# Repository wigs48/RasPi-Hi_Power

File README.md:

# RasPi-Hi_Power
8 channel MOSFET switch hat for RPi

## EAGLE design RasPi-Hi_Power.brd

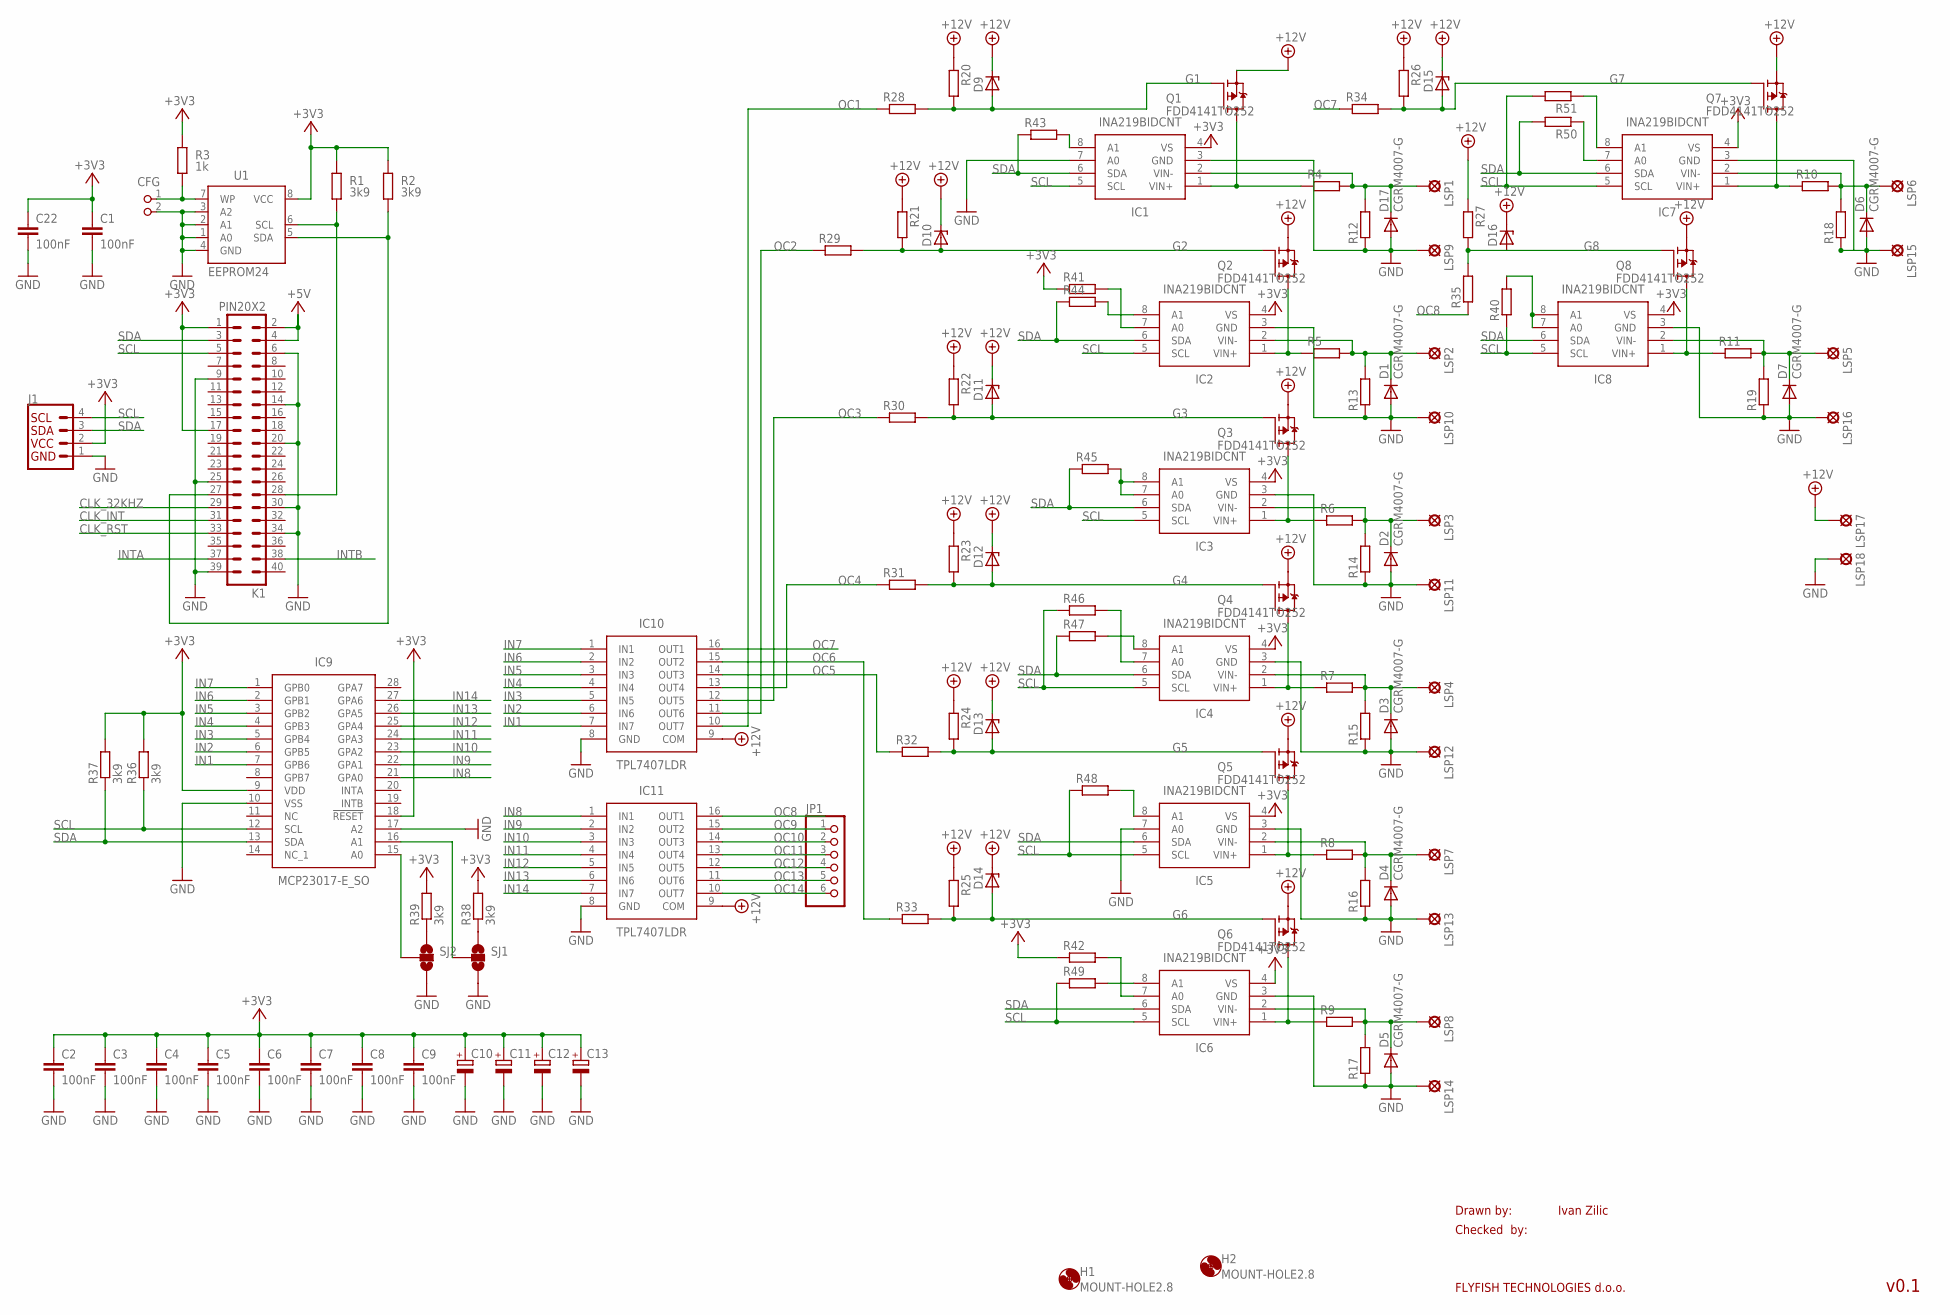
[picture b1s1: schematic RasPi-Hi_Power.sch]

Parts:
C1, C2, C3, C4, C5, C6, C7, C8, C9, C22: 100nF; C0805K
C10, C11, C12, C13: CPOL-EUSMCD; SMC_D
CFG: PIN2_100; PIN_W_2
D1, D2, D3, D4, D5, D6, D7, D17: CGRM4007-G; SOD-123_MINI-SMA
D9, D10, D11, D12, D13, D14, D15, D16: ZENER-DIODESOT23; SOT23
H1, H2: MOUNT-HOLE2.8; 2,8
IC1, IC2, IC3, IC4, IC5, IC6, IC7, IC8: INA219BIDCNT; SOT65P280X145-8N
IC9: MCP23017-E_SO; SOIC127P1030X265-28N
IC10, IC11: TPL7407LDR; SOIC127P600X175-16N
J1: I2C_STANDARD; 1X04
JP1: PINHD-1X6; 1X06
K1: PIN20X2; PIN_20X2
LSP1, LSP2, LSP3, LSP4, LSP5, LSP6, LSP7, LSP8, LSP9, LSP10, LSP11, LSP12, LSP13, LSP14, LSP15, LSP16, LSP17, LSP18: SE13
Q1, Q2, Q3, Q4, Q5, Q6, Q7, Q8: FDD4141TO252; TO252
R1, R2, R36, R37: 3k9; M0805; TOLERANCE 5%
R3: 1k; M0805; TOLERANCE 5%
R4, R5, R6, R7, R8, R9, R10, R11: R-EU_R1210; R1210
R12, R13, R14, R15, R16, R17, R18, R19, R20, R21, R22, R23, R24, R25, R26, R27, R28, R29, R30, R31, R32, R33, R34, R35, R41, R42, R43, R44, R45, R46, R47, R48, R49, R50, R51: R-EU_R0805; R0805
R38, R39: 3k9; R0603; TOLERANCE 5%
R40: R-EU_R0603; R0603
SJ1, SJ2: SOLDERJUMPER_2WAYT; SJ_2
U1: EEPROM24; SOIC8

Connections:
+3V3: C1.1, C2.1, C3.1, C4.1, C5.1, C6.1, C7.1, C8.1, C9.1, C10.+, C11.+, C12.+, C13.+, C22.1, IC1.4 (VS), IC2.4 (VS), IC3.4 (VS), IC4.4 (VS), IC5.4 (VS), IC6.4 (VS), IC7.4 (VS), IC8.4 (VS), IC9.9 (VDD), IC9.18 (!RESET), J1.2, K1.1, K1.17, R1.2, R2.2, R3.2, R36.2, R37.2, R38.2, R39.2, R41.1, R42.1, U1.8 (VCC)
+5V: K1.2, K1.4
+12V: D9.3 (C), D10.3 (C), D11.3 (C), D12.3 (C), D13.3 (C), D14.3 (C), D15.3 (C), D16.3 (C), IC10.9 (COM), IC11.9 (COM), LSP17.MP, Q1.2 (S), Q2.2 (S), Q3.2 (S), Q4.2 (S), Q5.2 (S), Q6.2 (S), Q7.2 (S), Q8.2 (S), R20.1, R21.1, R22.1, R23.1, R24.1, R25.1, R26.1, R27.1
CLK_32KHZ: K1.29
CLK_INT: K1.31
CLK_RST: K1.33
G1: D9.1 (A), Q1.1 (G), R20.2, R28.2
G2: D10.1 (A), Q2.1 (G), R21.2, R29.2
G3: D11.1 (A), Q3.1 (G), R22.2, R30.2
G4: D12.1 (A), Q4.1 (G), R23.2, R31.2
G5: D13.1 (A), Q5.1 (G), R24.2, R32.2
G6: D14.1 (A), Q6.1 (G), R25.2, R33.2
G7: D15.1 (A), Q7.1 (G), R26.2, R34.2
G8: D16.1 (A), Q8.1 (G), R27.2, R35.2
GND: C1.2, C2.2, C3.2, C4.2, C5.2, C6.2, C7.2, C8.2, C9.2, C10.-, C11.-, C12.-, C13.-, C22.2, CFG.2, D1.A, D2.A, D3.A, D4.A, D5.A, D6.A, D7.A, D17.A, IC1.3 (GND), IC1.7 (A0), IC2.3 (GND), IC3.3 (GND), IC4.3 (GND), IC5.3 (GND), IC5.7 (A0), IC6.3 (GND), IC7.3 (GND), IC8.3 (GND), IC9.10 (VSS), IC9.17 (A2), IC10.8 (GND), IC11.8 (GND), J1.1, K1.6, K1.9, K1.14, K1.20, K1.25, K1.30, K1.34, K1.39, LSP9.MP, LSP10.MP, LSP11.MP, LSP12.MP, LSP13.MP, LSP14.MP, LSP15.MP, LSP16.MP, LSP18.MP, R12.1, R13.1, R14.1, R15.1, R16.1, R17.1, R18.1, R19.1, SJ1.3, SJ2.3, U1.1 (A0), U1.2 (A1), U1.3 (A2), U1.4 (GND)
IN1: IC9.7 (GPB6), IC10.7 (IN7)
IN2: IC9.6 (GPB5), IC10.6 (IN6)
IN3: IC9.5 (GPB4), IC10.5 (IN5)
IN4: IC9.4 (GPB3), IC10.4 (IN4)
IN5: IC9.3 (GPB2), IC10.3 (IN3)
IN6: IC9.2 (GPB1), IC10.2 (IN2)
IN7: IC9.1 (GPB0), IC10.1 (IN1)
IN8: IC9.21 (GPA0), IC11.1 (IN1)
IN9: IC9.22 (GPA1), IC11.2 (IN2)
IN10: IC9.23 (GPA2), IC11.3 (IN3)
IN11: IC9.24 (GPA3), IC11.4 (IN4)
IN12: IC9.25 (GPA4), IC11.5 (IN5)
IN13: IC9.26 (GPA5), IC11.6 (IN6)
IN14: IC9.27 (GPA6), IC11.7 (IN7)
INTA: K1.37
INTB: K1.38
unnamed: IC8.1 (VIN+), Q8.3 (D), R11.1
unnamed: IC9.15 (A0), SJ2.2
unnamed: CFG.1, R3.1, U1.7 (WP)
unnamed: IC7.1 (VIN+), Q7.3 (D), R10.1
unnamed: D6.C, IC7.2 (VIN-), LSP6.MP, R10.2, R18.2
unnamed: IC3.1 (VIN+), Q3.3 (D), R6.1
unnamed: IC4.1 (VIN+), Q4.3 (D), R7.1
unnamed: D3.C, IC4.2 (VIN-), LSP4.MP, R7.2, R15.2
unnamed: D2.C, IC3.2 (VIN-), LSP3.MP, R6.2, R14.2
unnamed: IC2.1 (VIN+), Q2.3 (D), R5.1
unnamed: D1.C, IC2.2 (VIN-), LSP2.MP, R5.2, R13.2
unnamed: IC5.1 (VIN+), Q5.3 (D), R8.1
unnamed: D4.C, IC5.2 (VIN-), LSP7.MP, R8.2, R16.2
unnamed: IC6.1 (VIN+), Q6.3 (D), R9.1
unnamed: D5.C, IC6.2 (VIN-), LSP8.MP, R9.2, R17.2
unnamed: K1.28, R1.1, U1.6 (SCL)
unnamed: IC1.1 (VIN+), Q1.3 (D), R4.1
unnamed: D17.C, IC1.2 (VIN-), LSP1.MP, R4.2, R12.2
unnamed: IC9.16 (A1), SJ1.2
unnamed: R38.1, SJ1.1
unnamed: R39.1, SJ2.1
unnamed: K1.27, R2.1, U1.5 (SDA)
unnamed: IC8.7 (A0), IC8.8 (A1), R40.2
unnamed: IC2.7 (A0), R41.2
unnamed: IC6.7 (A0), R42.2
unnamed: IC1.8 (A1), R43.2
unnamed: IC2.8 (A1), R44.2
unnamed: IC3.7 (A0), IC3.8 (A1), R45.2
unnamed: IC4.8 (A1), R47.2
unnamed: IC4.7 (A0), R46.2
unnamed: IC5.8 (A1), R48.2
unnamed: IC6.8 (A1), R49.2
unnamed: IC7.8 (A1), R51.1
unnamed: IC7.7 (A0), R50.1
OC1: IC10.10 (OUT7), R28.1
OC2: IC10.11 (OUT6), R29.1
OC3: IC10.12 (OUT5), R30.1
OC4: IC10.13 (OUT4), R31.1
OC5: IC10.14 (OUT3), R32.1
OC6: IC10.15 (OUT2), R33.1
OC7: IC10.16 (OUT1), R34.1
OC8: IC11.16 (OUT1), R35.1
OC9: IC11.15 (OUT2), JP1.1
OC10: IC11.14 (OUT3), JP1.2
OC11: IC11.13 (OUT4), JP1.3
OC12: IC11.12 (OUT5), JP1.4
OC13: IC11.11 (OUT6), JP1.5
OC14: IC11.10 (OUT7), JP1.6
OUT8: D7.C, IC8.2 (VIN-), LSP5.MP, R11.2, R19.2
SCL: IC1.5 (SCL), IC2.5 (SCL), IC3.5 (SCL), IC4.5 (SCL), IC5.5 (SCL), IC6.5 (SCL), IC7.5 (SCL), IC8.5 (SCL), IC9.12 (SCL), J1.4, K1.5, R36.1, R40.1, R46.1, R48.1, R49.1, R51.2
SDA: IC1.6 (SDA), IC2.6 (SDA), IC3.6 (SDA), IC4.6 (SDA), IC5.6 (SDA), IC6.6 (SDA), IC7.6 (SDA), IC8.6 (SDA), IC9.13 (SDA), J1.3, K1.3, R37.1, R43.1, R44.1, R45.1, R47.1, R50.2

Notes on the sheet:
Drawn by:
Checked by:
FLYFISH TECHNOLOGIES d.o.o.
Ivan Zilic
v0.1

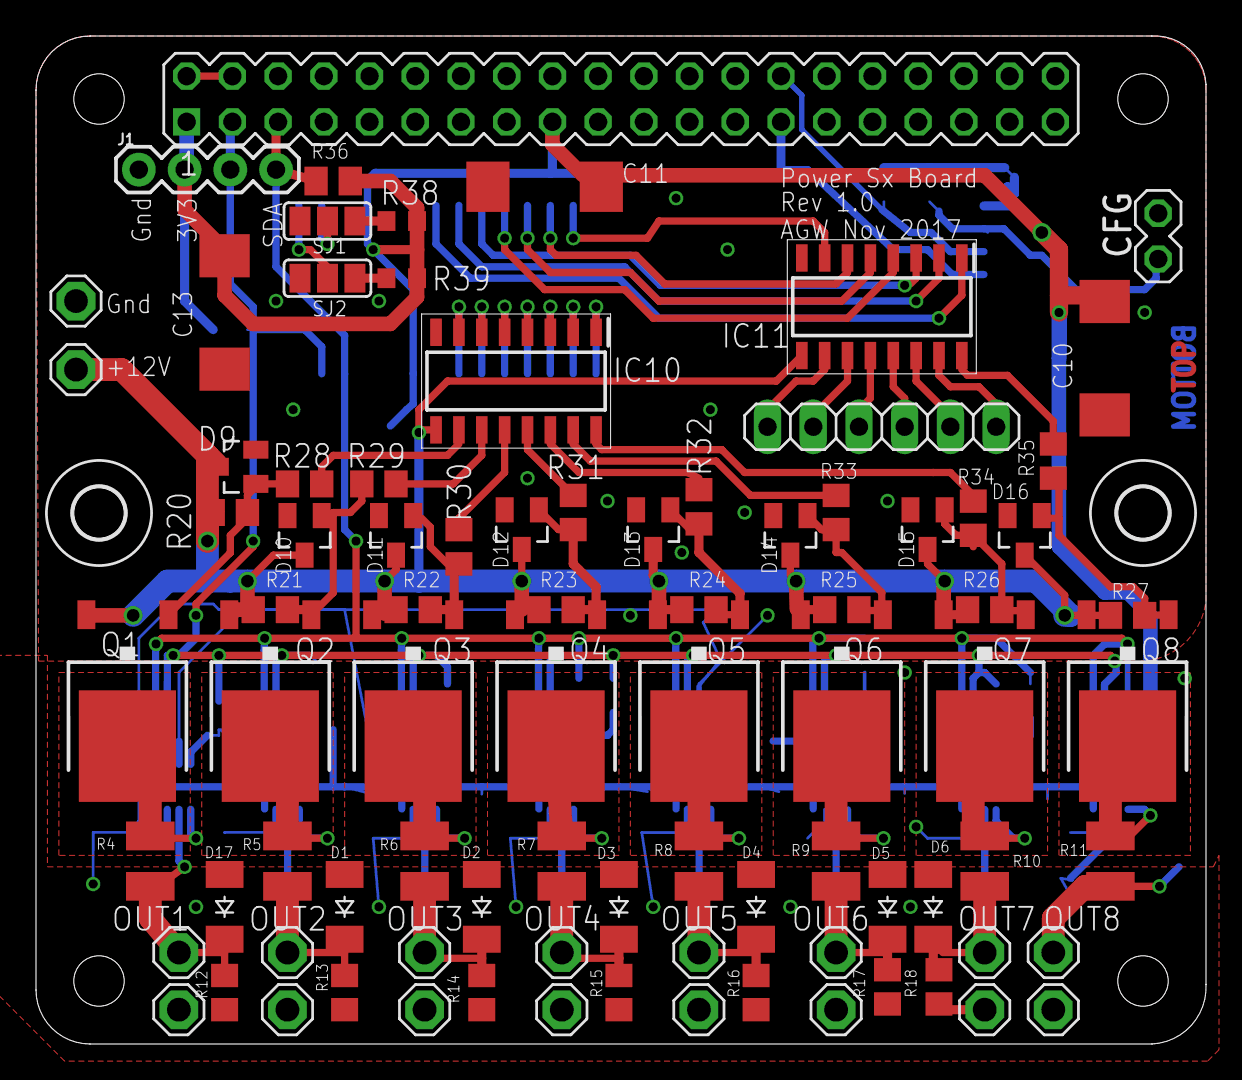
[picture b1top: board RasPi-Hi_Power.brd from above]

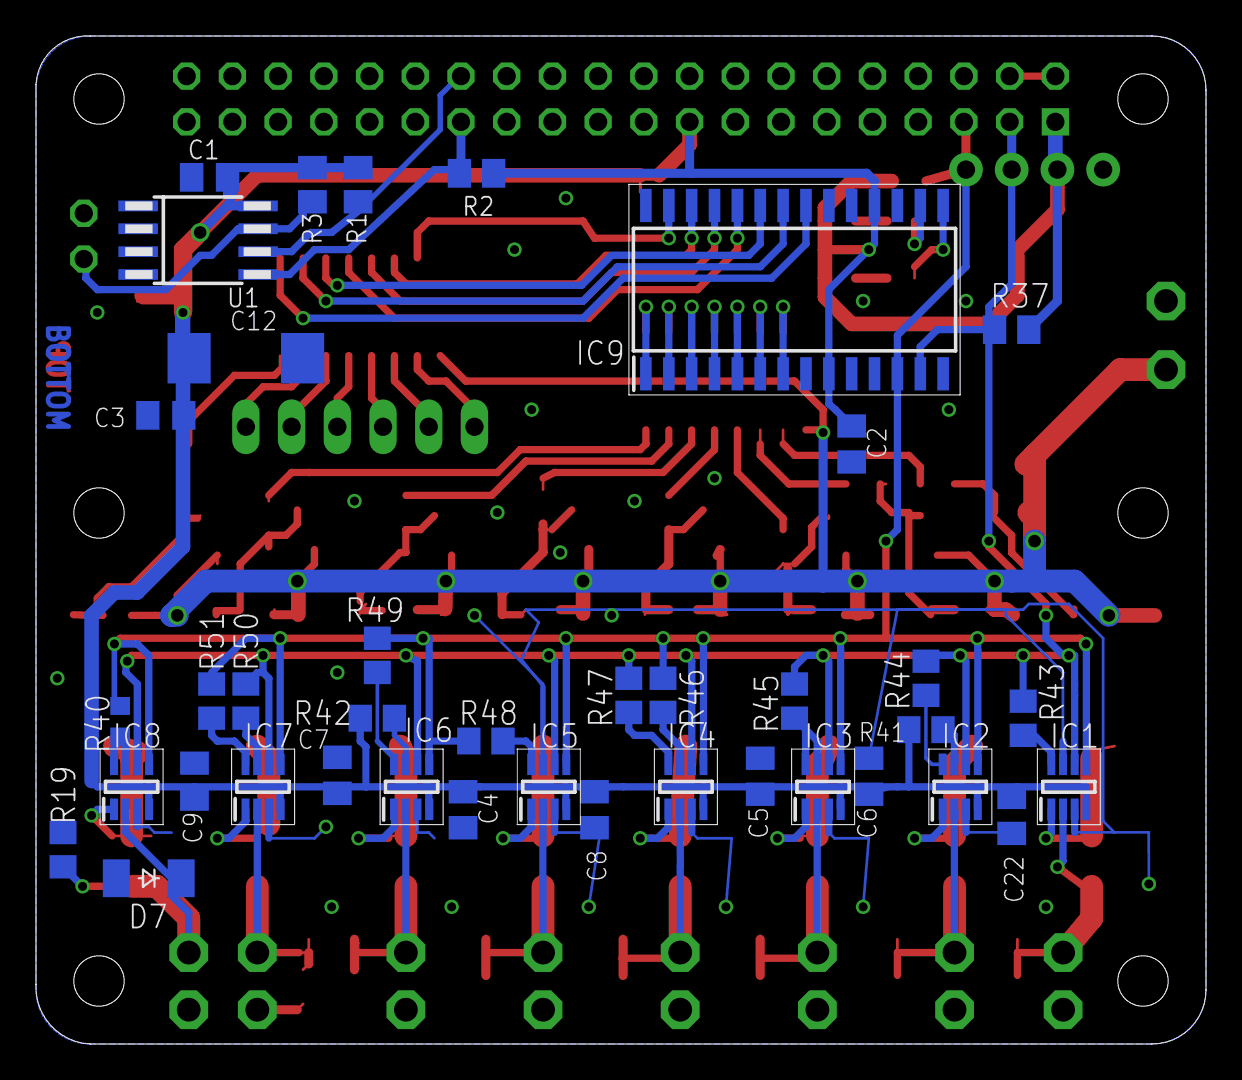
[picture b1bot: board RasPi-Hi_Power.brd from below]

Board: 2 copper layers, 65.0 x 56.0 mm, 127 parts (39 on the bottom side), 77 nets.

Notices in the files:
parts and their libraries:
SparkFun-Connectors: Licensing: Creative Commons ShareAlike 4.0 International - https://creativecommons.org/licenses/by-sa/4.0
